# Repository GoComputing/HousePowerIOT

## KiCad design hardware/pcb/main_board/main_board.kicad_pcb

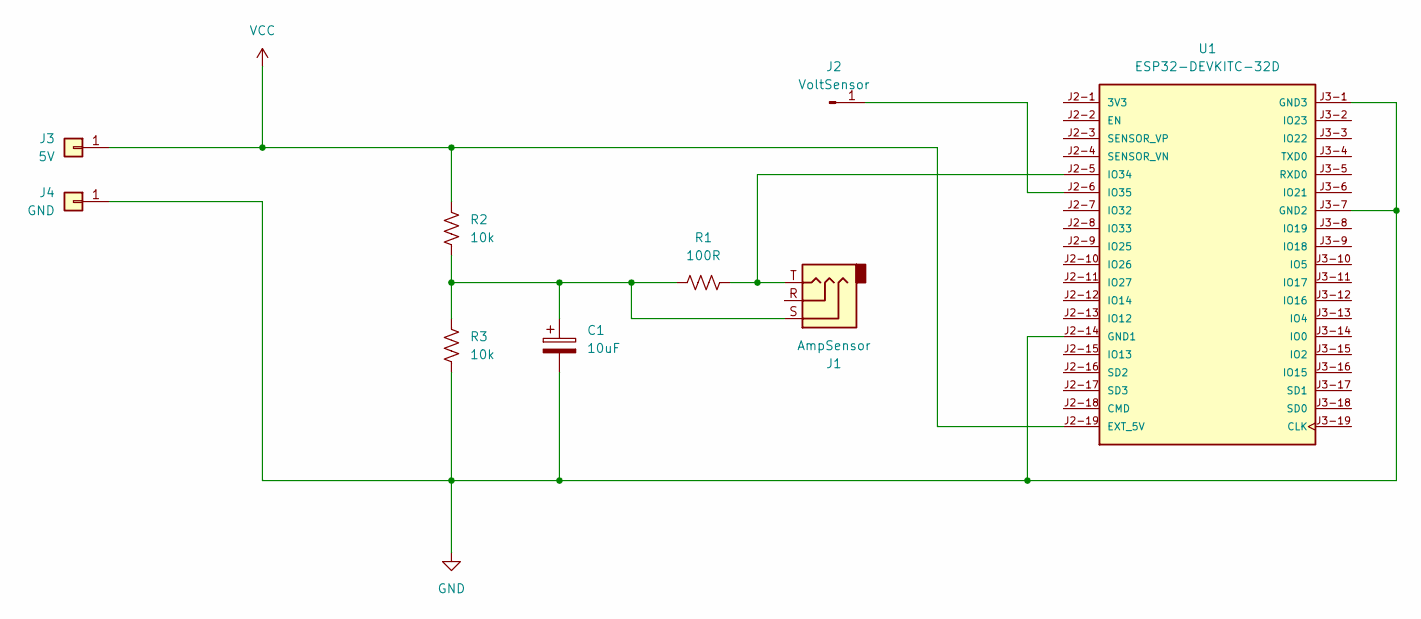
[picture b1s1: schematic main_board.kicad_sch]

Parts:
C1: 10uF; CP_Radial_D8.0mm_P3.80mm
J1: AmpSensor; Jack_3.5mm_CUI_SJ1-3533NG_Horizontal_CircularHoles
J2: VoltSensor; PinHeader_1x01_P1.00mm_Vertical
J3: 5V; PinHeader_1x01_P1.00mm_Vertical
J4: GND; PinHeader_1x01_P1.00mm_Vertical
R1: 100R; R_Axial_DIN0207_L6.3mm_D2.5mm_P10.16mm_Horizontal
R2, R3: 10k; R_Axial_DIN0207_L6.3mm_D2.5mm_P10.16mm_Horizontal
U1: ESP32-DEVKITC-32D; MODULE_ESP32-DEVKITC-32D; PARTREV V4

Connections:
GND: C1.2, J4.1, R3.2, U1.J2-14 (GND1), U1.J3-1 (GND3), U1.J3-7 (GND2)
unnamed: C1.1, J1.S, R1.2, R2.2, R3.1
unnamed: J2.1, U1.J2-6 (IO35)
unnamed: J1.T, R1.1, U1.J2-5 (IO34)
VCC: J3.1, R2.1, U1.J2-19 (EXT_5V)

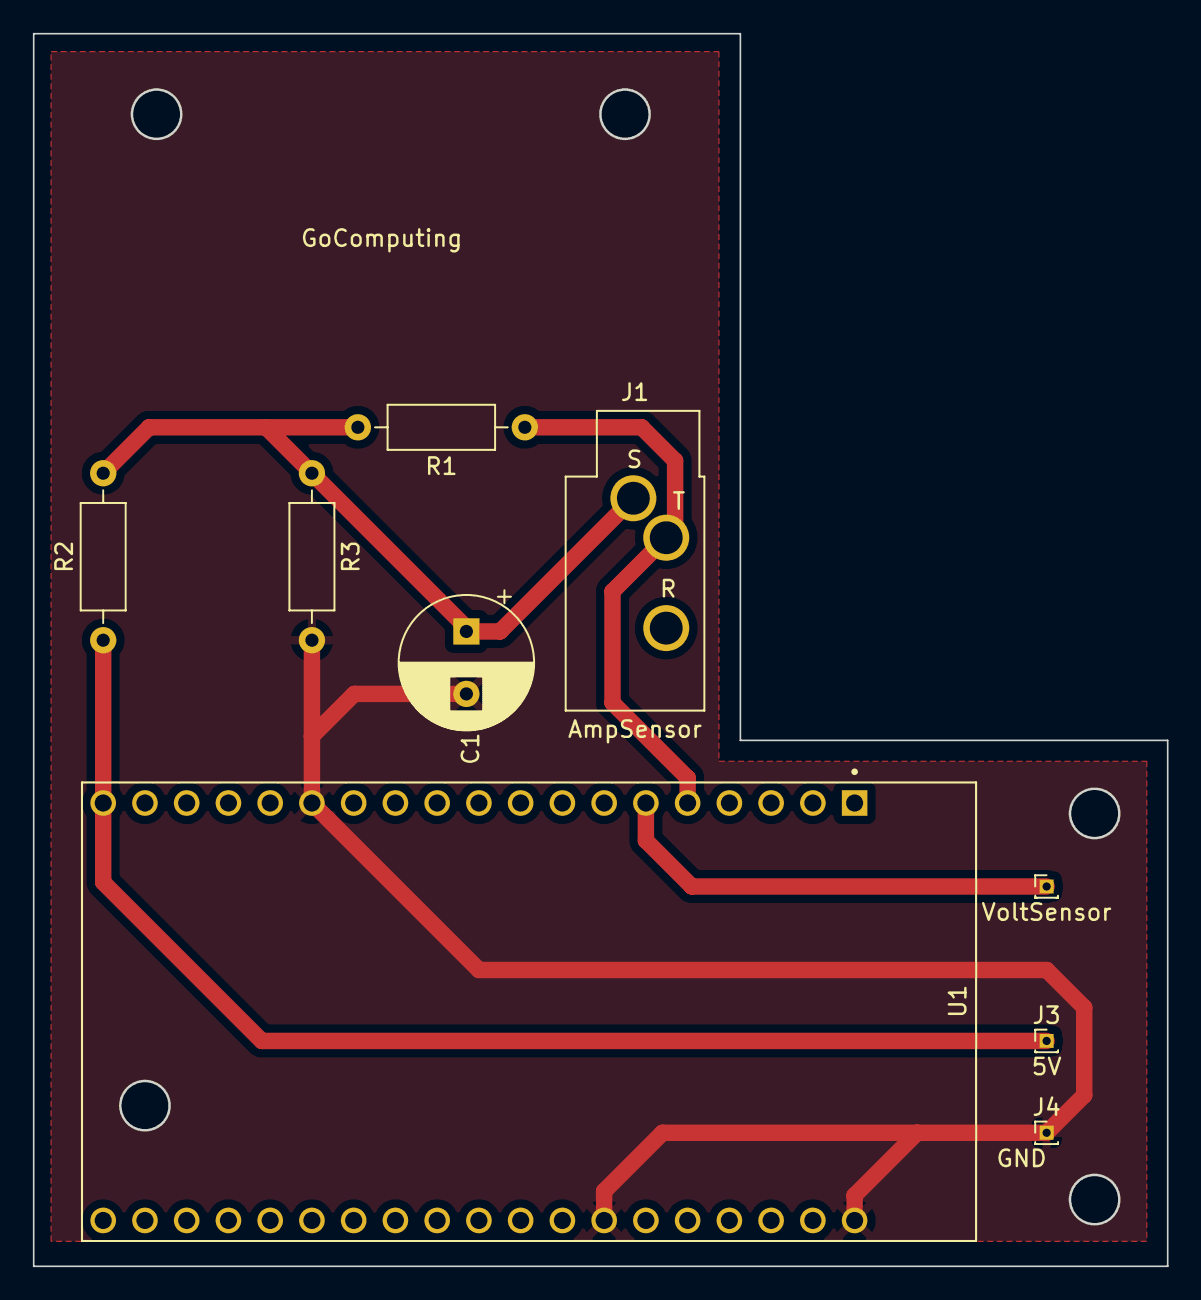
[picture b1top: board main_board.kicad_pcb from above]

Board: 2 copper layers, 68.9 x 74.9 mm, 9 parts (0 on the bottom side), 5 nets.

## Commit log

2024-02-11 Connected to InfluxDB database and pushed random values
2024-02-18 Initial schematic
2024-02-18 Binded schematic components to PCB symbols
2024-02-18 Generated PCB
2024-02-18 Generated gerber files
2024-02-19 Changed screw holes diameter to 3mm
2024-03-01 Right main PCB support model
2024-03-15 Power supply support
2024-03-15 Voltage sensor support
2024-03-16 Wires support
2024-03-16 Read sensor values
2024-03-16 Second version of power supply support
2024-03-26 Initial Ionic app project
2024-03-26 Updated names and icons
2024-03-26 General template for the plots
2024-03-26 Integrated with Android
2024-03-27 Energy observer implementation
2024-03-27 Updated chart with actual values
2024-03-27 Updated secrets templates
2024-03-28 Power consumption plot
2024-03-28 Implemented new algorithm to read sensors
